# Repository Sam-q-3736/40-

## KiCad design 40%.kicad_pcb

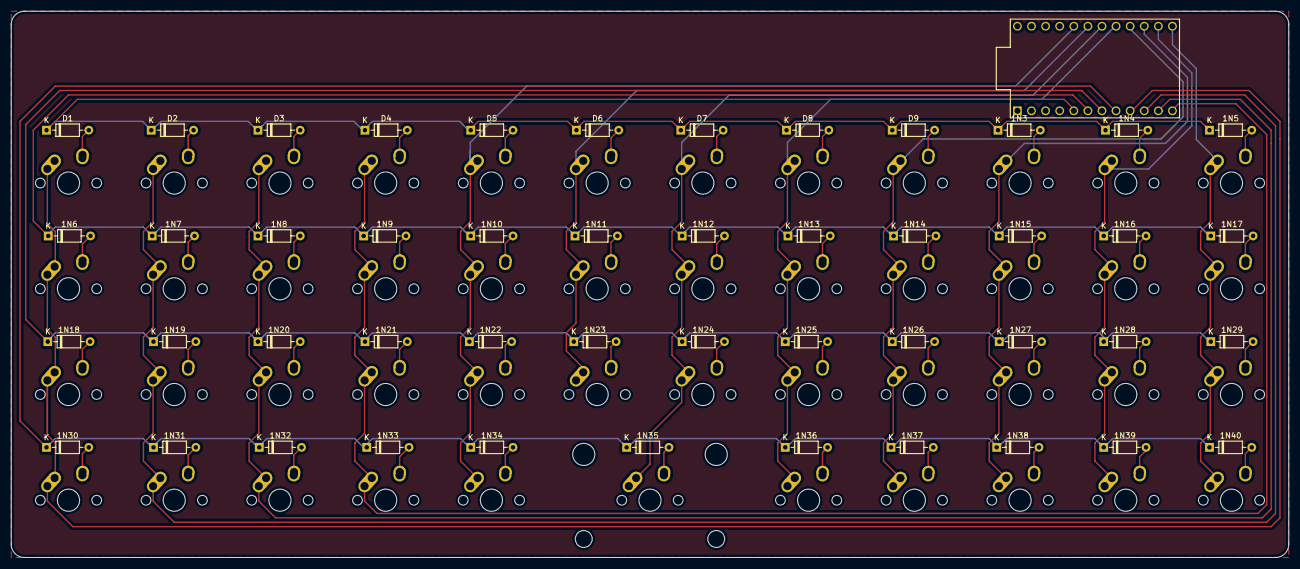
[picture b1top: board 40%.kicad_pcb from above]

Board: 2 copper layers, 230.2 x 98.4 mm, 95 parts (0 on the bottom side), 63 nets.

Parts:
1N3, 1N4, 1N5, 1N6, 1N7, 1N8, 1N9, 1N10, 1N11, 1N12, 1N13, 1N14, 1N15, 1N16, 1N17, 1N18, 1N19, 1N20, 1N21, 1N22, 1N23, 1N24, 1N25, 1N26, 1N27, 1N28, 1N29, 1N30, 1N31, 1N32, 1N33, 1N34, 1N35, 1N36, 1N37, 1N38, 1N39, 1N40: D_Small; D_DO-35_SOD27_P7.62mm_Horizontal
D1, D2, D3, D4, D5, D6, D7, D8, D9: D_Small; D_DO-35_SOD27_P7.62mm_Horizontal
a1: MX-NoLED; MX-1U-NoLED
alt1: MX-NoLED; MX-1U-NoLED
b1: MX-NoLED; MX-1U-NoLED
c1: MX-NoLED; MX-1U-NoLED
comma1: MX-NoLED; MX-1U-NoLED
ctrl1: MX-NoLED; MX-1U-NoLED
d1: MX-NoLED; MX-1U-NoLED
delete1: MX-NoLED; MX-1U-NoLED
down1: MX-NoLED; MX-1U-NoLED
e1: MX-NoLED; MX-1U-NoLED
enter1: MX-NoLED; MX-1U-NoLED
esc1: MX-NoLED; MX-1U-NoLED
f1: MX-NoLED; MX-1U-NoLED
fn1: MX-NoLED; MX-1U-NoLED
g1: MX-NoLED; MX-1U-NoLED
h1: MX-NoLED; MX-1U-NoLED
i1: MX-NoLED; MX-1U-NoLED
j1: MX-NoLED; MX-1U-NoLED
k1: MX-NoLED; MX-1U-NoLED
l1: MX-NoLED; MX-1U-NoLED
layer1, layer2: MX-NoLED; MX-1U-NoLED
left1: MX-NoLED; MX-1U-NoLED
m1: MX-NoLED; MX-1U-NoLED
n1: MX-NoLED; MX-1U-NoLED
o1: MX-NoLED; MX-1U-NoLED
p1: MX-NoLED; MX-1U-NoLED
period1: MX-NoLED; MX-1U-NoLED
promicro1: ProMicro
q1: MX-NoLED; MX-1U-NoLED
r1: MX-NoLED; MX-1U-NoLED
reset1: MX-NoLED; MX-1U-NoLED
right1: MX-NoLED; MX-1U-NoLED
s1: MX-NoLED; MX-1U-NoLED
semicolon1: MX-NoLED; MX-1U-NoLED
shift1: MX-NoLED; MX-1U-NoLED
slash1: MX-NoLED; MX-1U-NoLED
space1: MX-NoLED; MX-2U-ReversedStabilizers-NoLED
t1: MX-NoLED; MX-1U-NoLED
tab1: MX-NoLED; MX-1U-NoLED
u1: MX-NoLED; MX-1U-NoLED
up1: MX-NoLED; MX-1U-NoLED
v1: MX-NoLED; MX-1U-NoLED
w1: MX-NoLED; MX-1U-NoLED
win1: MX-NoLED; MX-1U-NoLED
x1: MX-NoLED; MX-1U-NoLED
y1: MX-NoLED; MX-1U-NoLED
z1: MX-NoLED; MX-1U-NoLED

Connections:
unnamed: 1N3.2, o1.2
unnamed: 1N4.2, p1.2
unnamed: 1N5.2, delete1.2
unnamed: 1N6.2, tab1.2
unnamed: 1N7.2, a1.2
unnamed: 1N8.2, s1.2
unnamed: 1N9.2, d1.2
unnamed: 1N10.2, f1.2
unnamed: 1N11.2, g1.2
unnamed: 1N12.2, h1.2
unnamed: 1N13.2, j1.2
unnamed: 1N14.2, k1.2
unnamed: 1N15.2, l1.2
unnamed: 1N16.2, semicolon1.2
unnamed: 1N17.2, enter1.2
unnamed: 1N18.2, shift1.2
unnamed: 1N19.2, z1.2
unnamed: 1N20.2, x1.2
unnamed: 1N21.2, c1.2
unnamed: 1N22.2, v1.2
unnamed: 1N23.2, b1.2
unnamed: 1N24.2, n1.2
unnamed: 1N25.2, m1.2
unnamed: 1N26.2, comma1.2
unnamed: 1N27.2, period1.2
unnamed: 1N28.2, up1.2
unnamed: 1N29.2, slash1.2
unnamed: 1N30.2, ctrl1.2
unnamed: 1N31.2, win1.2
unnamed: 1N32.2, alt1.2
unnamed: 1N33.2, fn1.2
unnamed: 1N34.2, layer1.2
unnamed: 1N35.2, space1.2
unnamed: 1N36.2, layer2.2
unnamed: 1N37.2, reset1.2
unnamed: 1N38.2, left1.2
unnamed: 1N39.2, down1.2
unnamed: 1N40.2, right1.2
unnamed: D1.2, esc1.2
unnamed: D2.2, q1.2
unnamed: D3.2, w1.2
unnamed: D4.2, e1.2
unnamed: D5.2, r1.2
unnamed: D6.2, t1.2
unnamed: D7.2, y1.2
unnamed: D8.2, u1.2
unnamed: D9.2, i1.2
col0: ctrl1.1, esc1.1, promicro1.9, shift1.1, tab1.1
col1: a1.1, promicro1.10, q1.1, win1.1, z1.1
col2: alt1.1, promicro1.11, s1.1, w1.1, x1.1
col3: c1.1, d1.1, e1.1, fn1.1, promicro1.12
col4: f1.1, layer1.1, promicro1.20, r1.1, v1.1
col5: b1.1, g1.1, promicro1.19, t1.1
col6: h1.1, n1.1, promicro1.18, space1.1, y1.1
col7: j1.1, layer2.1, m1.1, promicro1.17, u1.1
col8: comma1.1, i1.1, k1.1, promicro1.16, reset1.1
col9: l1.1, left1.1, o1.1, period1.1, promicro1.15
col10: down1.1, p1.1, promicro1.14, semicolon1.1, up1.1
col11: delete1.1, enter1.1, promicro1.13, right1.1, slash1.1
row0: 1N3.1, 1N4.1, 1N5.1, D1.1, D2.1, D3.1, D4.1, D5.1, D6.1, D7.1, D8.1, D9.1, promicro1.5
row1: 1N6.1, 1N7.1, 1N8.1, 1N9.1, 1N10.1, 1N11.1, 1N12.1, 1N13.1, 1N14.1, 1N15.1, 1N16.1, 1N17.1, promicro1.6
row2: 1N18.1, 1N19.1, 1N20.1, 1N21.1, 1N22.1, 1N23.1, 1N24.1, 1N25.1, 1N26.1, 1N27.1, 1N28.1, 1N29.1, promicro1.7
row3: 1N30.1, 1N31.1, 1N32.1, 1N33.1, 1N34.1, 1N35.1, 1N36.1, 1N37.1, 1N38.1, 1N39.1, 1N40.1, promicro1.8

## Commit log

2022-01-10 PCB and plate kicad files
2022-01-10 finalized some things, slight edits to prep for production
